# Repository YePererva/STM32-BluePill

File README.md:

# BluePill with USB type C

**NB! :** This a Work In Progress repository.

Here, I wanted to made a modification of the highly popular [STM32F103C8T6](https://www.st.com/resource/en/datasheet/stm32f103c8.pdf) development board, widely referred as [BluePill](https://stm32-base.org/boards/STM32F103C8T6-Blue-Pill.html).

The changes, I want(ed) to implement, are:
- replace the micro-USB slot with USB type C connector
- replace the 4-pin SWD programming connector with STDC-14 connector for compatibility with [ST-Link V3 mini](https://www.st.com/en/development-tools/stlink-v3mini.html) programmer
  - It should be compatible with 10-pin ARM cortex programming connector
  - I want to wire the SWO connectivity for more debug options
- Add [QWIIC](https://www.sparkfun.com/products/14417) connector for easier I2C sensor boards connection (like on [Sparkfun](https://www.sparkfun.com/qwiic#products) boards)
- replace the jumpers for boot options with tactile buttons (like on another variation of BluePill made by a seller from [TaoBao](https://ydsd1.oss-cn-shenzhen.aliyuncs.com/STM32F1/103C8V1.1.rar) )
- add power protection to USB against external power source (thinking between diode or MOSFET connectivity)
- add the RTC power isolation
- replace the 8Mhz crystal with SMD (maybe, like on [MapleMini](https://github.com/leaflabs/maplemini) )
- add a option to use microcontroller not only in LQFP48 package, but UFQFPN48 package (alike [STM32F103CBU6](https://www.st.com/resource/en/datasheet/cd00161566.pdf))
- Replace the Power regulator. \
  Various versions of BluePill utilize either [RT9193-33](https://web.archive.org/web/20190316155227/http://wiki.stm32duino.com/index.php?title=Blue_Pill) or [TX6211B](https://stm32-base.org/boards/STM32F103C8T6-Blue-Pill), which are documented as < 300 mA power supply, but can overheat if used >100 mA.

With all of that, I also want to keep pin-to-pin compatibility with original BluePill and the final size of the board.

## What is inside the repository
- `project files` : folder with BluePill projects, implemented in KiCAD
  - `classic` : the "traditional" BluePill board, with some schematic fixes (wrong resistor value for USB pull-up, extra capacitor, etc.) and some "cosmetic" changes on board.
  - `reforged` : the board with fixes and functionality I want to add
- `references` : some references of schematics / issues / layouts I found

## Why I want to do it
- I want to practice with KiCAD
- I want electronics to be my hobby
- It is fun for me

# Afterwords
1. If you are looking for higher performance, take a look at STM32F411CE or STM32F401CC boards in similar form-factor (however, with different pinout) in [this](https://github.com/WeActTC/MiniF4-STM32F4x1) repository by WeAct Team.

2. WeAct Team also released a similar project for STM32F103CxT6 microcontroller and called it a [BluePill Plus](https://github.com/WeActTC/BluePill-Plus) with some differences:
  - not pin-to-pin compatible (right top pin near USB port is `+5V`, not `GND`)
  - the user LED moved to `PB2` pin, while should be attached `PC13`
  - extra user button, attached to `PA0`
  - extra solder place for SPI-Flash IC

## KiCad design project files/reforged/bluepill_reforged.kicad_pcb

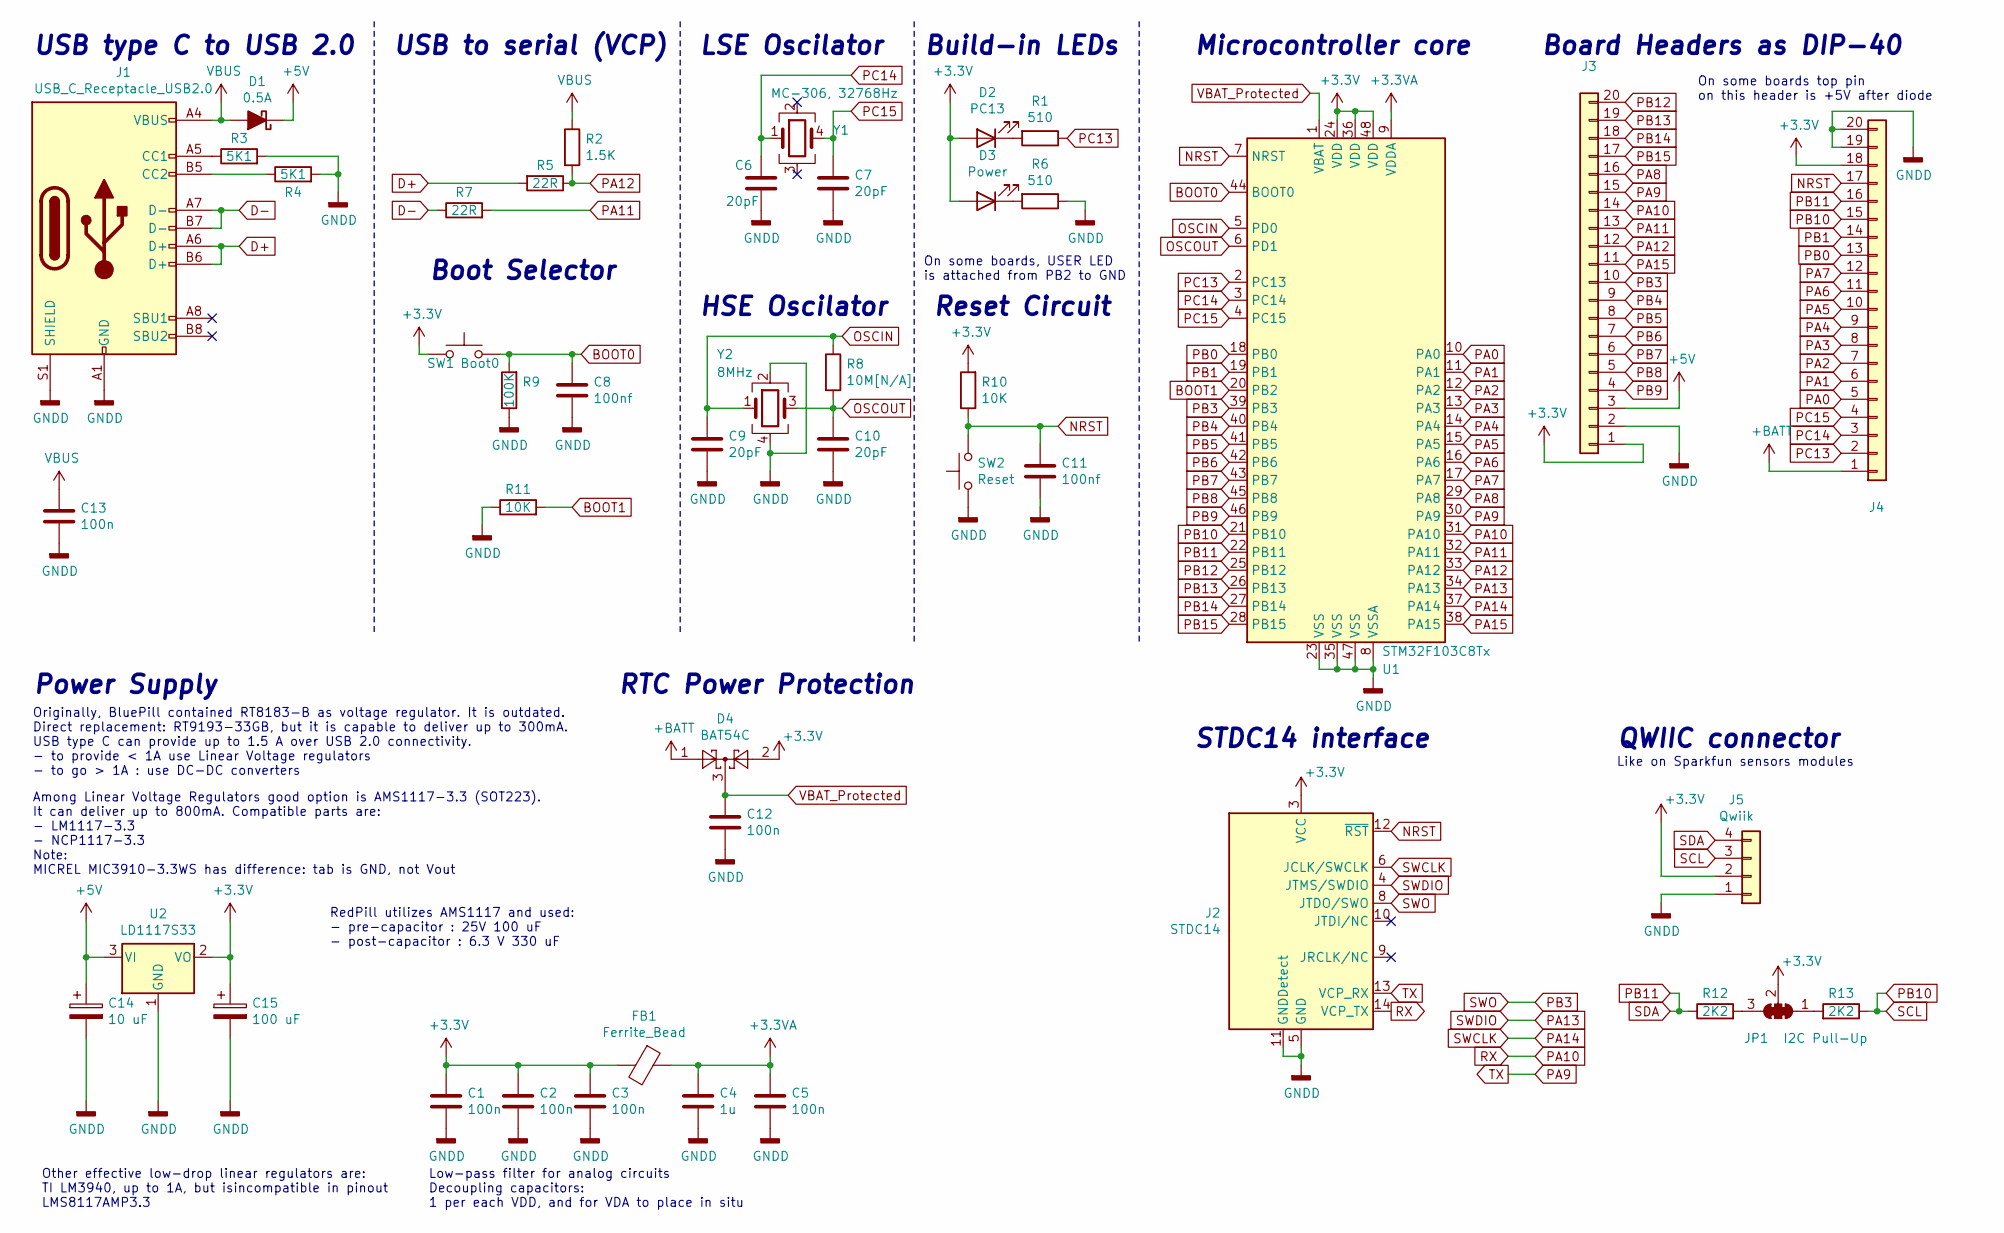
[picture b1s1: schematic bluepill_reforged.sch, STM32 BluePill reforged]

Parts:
C1, C2, C3, C5, C12, C13: 100n; C_0603_1608Metric
C4: 1u; C_0603_1608Metric
C6, C7, C9, C10: 20pF; C_0603_1608Metric
C8, C11: 100nf; C_0603_1608Metric
C14: 10 uF; CP_EIA-3528-12_Kemet-T
C15: 100 uF; CP_EIA-3528-12_Kemet-T
D1: 0.5A; D_SOD-128
D2: PC13; LED_0603_1608Metric_Castellated
D3: Power; LED_0603_1608Metric_Castellated
D4: BAT54C; SOT-23
FB1: Ferrite_Bead; L_0805_2012Metric
J1: USB_C_Receptacle_USB2.0; USB_C_Receptacle_Palconn_UTC16-G
J2: STDC14; PinHeader_2x07_P1.27mm_Vertical_SMD
J3: Left Castellation; PinHeader_1x20_P2.54mm_Vertical
J4: Right Castellation; PinHeader_1x20_P2.54mm_Vertical
J5: Qwiik; JST_SH_SM04B-SRSS-TB_1x04-1MP_P1.00mm_Horizontal
JP1: I2C Pull-Up; SolderJumper-3_P2.0mm_Open_TrianglePad1.0x1.5mm_NumberLabels
R1, R6: 510; R_0603_1608Metric
R2: 1.5K; R_0603_1608Metric
R3, R4: 5K1; R_0603_1608Metric
R5, R7: 22R; R_0603_1608Metric
R8: 10M[N/A]; R_0603_1608Metric
R9: 100K; R_0603_1608Metric
R10, R11: 10K; R_0603_1608Metric
R12, R13: 2K2; R_0603_1608Metric
SW1: Boot0; SW_SPST_B3U-1000P
SW2: Reset; SW_SPST_B3U-1000P
U1: STM32F103C8Tx; LQFP-48_7x7mm_P0.5mm
U2: LD1117S33; SOT-223-3_TabPin2
Y1: MC-306, 32768Hz; Crystal_SMD_SeikoEpson_MC306-4Pin_8.0x3.2mm
Y2: 8MHz; Crystal_SMD_TXC_7M-4Pin_3.2x2.5mm

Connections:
+3.3VA: C4.1, C5.1, FB1.1, U1.9 (VDDA)
+3V3: C1.1, C2.1, C3.1, C15.1, D2.2 (A), D3.2 (A), D4.2, FB1.2, J2.3 (VCC), J3.1, J4.18, J5.2, JP1.2 (C), R10.2, SW1.1, U1.24 (VDD), U1.36 (VDD), U1.48 (VDD), U2.2 (VO)
+5V: C14.1, D1.1 (K), J3.3, U2.3 (VI)
+BATT: D4.1, J4.1
BOOT0: C8.1, R9.2, SW1.2, U1.44 (BOOT0)
BOOT1: R11.2, U1.20 (PB2)
D+: J1.A6 (D+), J1.B6 (D+), R5.2
D-: J1.A7 (D-), J1.B7 (D-), R7.1
GNDD: C1.2, C2.2, C3.2, C4.2, C5.2, C6.2, C7.2, C8.2, C9.2, C10.2, C11.2, C12.2, C13.2, C14.2, C15.2, J1.A1 (GND), J1.A12 (GND), J1.B1 (GND), J1.B12 (GND), J1.S1 (SHIELD), J2.5 (GND), J2.7 (GND), J2.11 (GNDDetect), J3.2, J4.19, J4.20, J5.1, R3.2, R4.2, R6.1, R9.1, R11.1, SW2.1, U1.8 (VSSA), U1.23 (VSS), U1.35 (VSS), U1.47 (VSS), U2.1 (GND), Y2.2, Y2.4
NRST: C11.1, J2.12 (~RST), J4.17, R10.1, SW2.2, U1.7 (NRST)
unnamed: D2.1 (K), R1.2
unnamed: D3.1 (K), R6.2
unnamed: J1.A5 (CC1), R3.1
unnamed: J1.B5 (CC2), R4.1
unnamed: JP1.1 (A), R13.2
unnamed: JP1.3 (B), R12.2
OSCIN: C9.1, R8.1, U1.5 (PD0), Y2.1
OSCOUT: C10.1, R8.2, U1.6 (PD1), Y2.3
PA0: J4.5, U1.10 (PA0)
PA1: J4.6, U1.11 (PA1)
PA2: J4.7, U1.12 (PA2)
PA3: J4.8, U1.13 (PA3)
PA4: J4.9, U1.14 (PA4)
PA5: J4.10, U1.15 (PA5)
PA6: J4.11, U1.16 (PA6)
PA7: J4.12, U1.17 (PA7)
PA8: J3.16, U1.29 (PA8)
PA9: J2.13 (VCP_RX), J3.15, U1.30 (PA9)
PA10: J2.14 (VCP_TX), J3.14, U1.31 (PA10)
PA11: J3.13, R7.2, U1.32 (PA11)
PA12: J3.12, R2.2, R5.1, U1.33 (PA12)
PA13: J2.4 (JTMS/SWDIO), U1.34 (PA13)
PA14: J2.6 (JCLK/SWCLK), U1.37 (PA14)
PA15: J3.11, U1.38 (PA15)
PB0: J4.13, U1.18 (PB0)
PB1: J4.14, U1.19 (PB1)
PB3: J2.8 (JTDO/SWO), J3.10, U1.39 (PB3)
PB4: J3.9, U1.40 (PB4)
PB5: J3.8, U1.41 (PB5)
PB6: J3.7, U1.42 (PB6)
PB7: J3.6, U1.43 (PB7)
PB8: J3.5, U1.45 (PB8)
PB9: J3.4, U1.46 (PB9)
PB10: J4.15, J5.3, R13.1, U1.21 (PB10)
PB11: J4.16, J5.4, R12.1, U1.22 (PB11)
PB12: J3.20, U1.25 (PB12)
PB13: J3.19, U1.26 (PB13)
PB14: J3.18, U1.27 (PB14)
PB15: J3.17, U1.28 (PB15)
PC13: J4.2, R1.1, U1.2 (PC13)
PC14: C6.1, J4.3, U1.3 (PC14), Y1.1
PC15: C7.1, J4.4, U1.4 (PC15), Y1.4
VBAT_Protected: C12.1, D4.3, U1.1 (VBAT)
VBUS: C13.1, D1.2 (A), J1.A4 (VBUS), J1.A9 (VBUS), J1.B4 (VBUS), J1.B9 (VBUS), R2.1

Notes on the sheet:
Build-in LEDs
LSE Oscilator
HSE Oscilator
Among Linear Voltage Regulators good option is AMS1117-3.3 (SOT223). It can deliver up to 800mA. Compatible parts are: - LM1117-3.3 - NCP1117-3.3 Note: MICREL MIC3910-3.3WS has difference: tab is GND, not Vout
Other effective low-drop linear regulators are: TI LM3940, up to 1A, but isincompatible in pinout LMS8117AMP3.3
RedPill utilizes AMS1117 and used: - pre-capacitor : 25V 100 uF - post-capacitor : 6.3 V 330 uF
Board Headers as DIP-40
USB type C to USB 2.0
USB to serial (VCP)
Boot Selector
Microcontroller core
STDC14 interface
RTC Power Protection
Reset Circuit
Low-pass filter for analog circuits Decoupling capacitors: 1 per each VDD, and for VDA to place in situ
Power Supply
Originally, BluePill contained RT8183-B as voltage regulator. It is outdated. Direct replacement: RT9193-33GB, but it is capable to deliver up to 300mA. USB type C can provide up to 1.5 A over USB 2.0 connectivity. - to provide < 1A use Linear Voltage regulators - to go > 1A : use DC-DC converters
On some boards, USER LED is attached from PB2 to GND
On some boards top pin on this header is +5V after diode
QWIIC connector
Like on Sparkfun sensors modules

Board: 2 copper layers, 45 parts (28 on the bottom side), 54 nets, no tracks yet.

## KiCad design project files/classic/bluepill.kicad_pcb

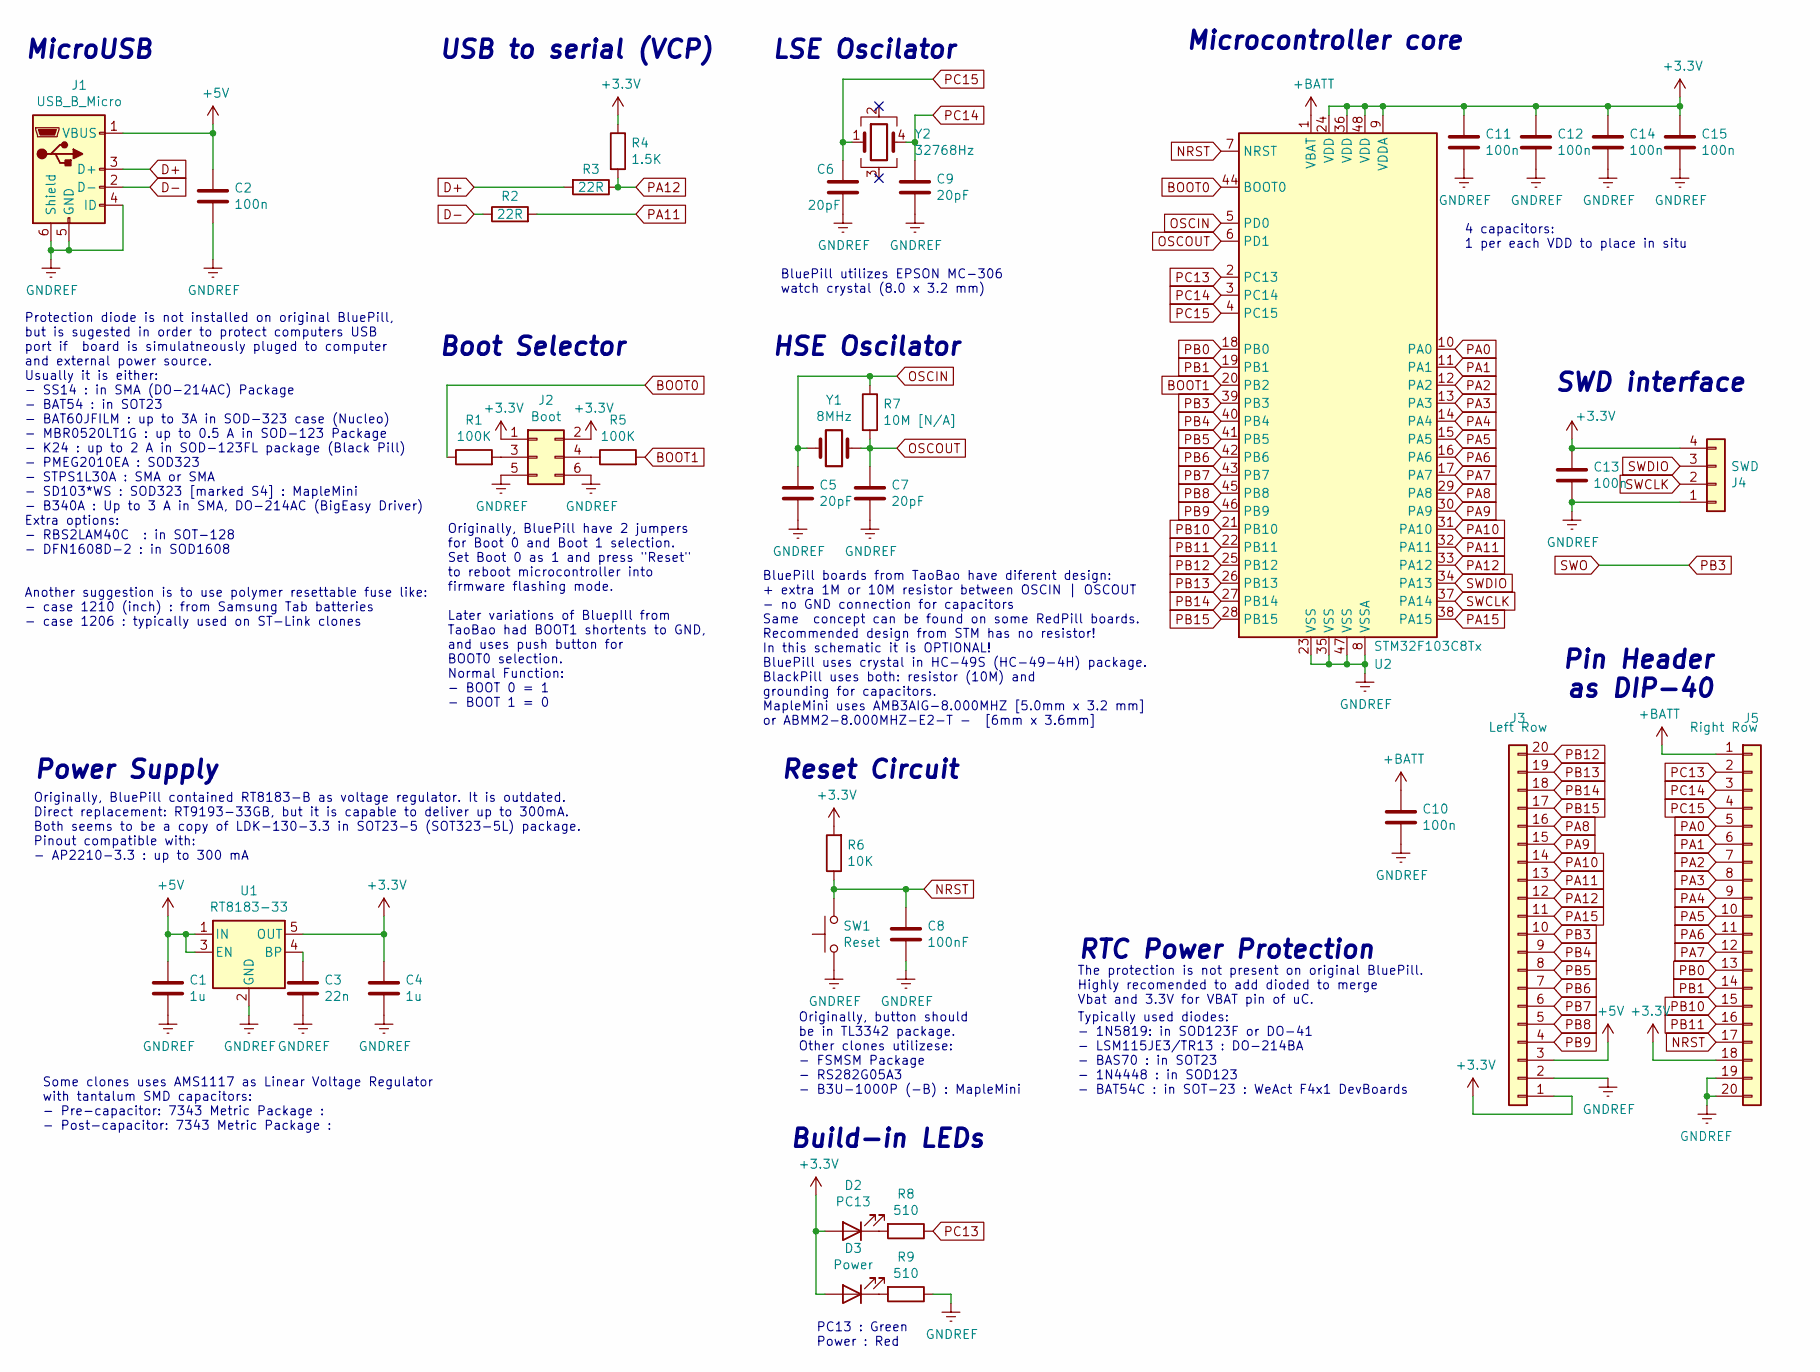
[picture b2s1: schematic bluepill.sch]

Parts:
C1: 1u; USB_Micro-B_Wuerth_629105150521
C2, C10, C11, C12, C13, C14, C15: 100n; C_0603_1608Metric
C3: 22n; C_0603_1608Metric
C4: 1u; C_0805_2012Metric
C5, C6, C7, C9: 20pF; C_0603_1608Metric
C8: 100nF; C_0603_1608Metric
D2: PC13; LED_0603_1608Metric_Castellated
D3: Power; LED_0603_1608Metric_Castellated
J1: USB_B_Micro
J2: Boot; PinHeader_2x03_P2.54mm_Vertical
J3: Left Row; PinHeader_1x20_P2.54mm_Vertical
J4: SWD; PinHeader_1x04_P2.54mm_Vertical
J5: Right Row; PinHeader_1x20_P2.54mm_Vertical
R1, R5: 100K; R_0603_1608Metric
R2, R3: 22R; R_0603_1608Metric
R4: 1.5K; R_0603_1608Metric
R6: 10K; R_0603_1608Metric
R7: 10M [N/A]; R_0603_1608Metric
R8, R9: 510; R_0603_1608Metric
SW1: Reset; SW_SPST_TL3342
U1: RT8183-33; SOT-353_SC-70-5
U2: STM32F103C8Tx; LQFP-48_7x7mm_P0.5mm
Y1: 8MHz; Crystal_HC49-4H_Vertical
Y2: 32768Hz; Crystal_SMD_SeikoEpson_MC306-4Pin_8.0x3.2mm

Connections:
+3V3: C4.2, C11.1, C12.1, C13.2, C14.1, C15.1, D2.2 (A), D3.2 (A), J2.1, J2.2, J3.1, J4.4, J5.18, R4.1, R6.2, U1.5 (OUT), U2.9 (VDDA), U2.24 (VDD), U2.36 (VDD), U2.48 (VDD)
+5V: C1.2, C2.1, J1.1 (VBUS), J3.3, U1.1 (IN), U1.3 (EN)
+BATT: C10.1, J5.1, U2.1 (VBAT)
BOOT0: R1.1, U2.44 (BOOT0)
BOOT1: R5.2, U2.20 (PB2)
D+: J1.3 (D+), R3.2
D-: J1.2 (D-), R2.1
GNDREF: C1.1, C2.2, C3.1, C4.1, C5.2, C6.2, C7.2, C8.2, C9.2, C10.2, C11.2, C12.2, C13.1, C14.2, C15.2, J1.4 (ID), J1.5 (GND), J1.6 (Shield), J2.5, J2.6, J3.2, J4.1, J5.19, J5.20, R9.1, SW1.1, U1.2 (GND), U2.8 (VSSA), U2.23 (VSS), U2.35 (VSS), U2.47 (VSS)
NRST: C8.1, J5.17, R6.1, SW1.2, U2.7 (NRST)
unnamed: C3.2, U1.4 (BP)
unnamed: D2.1 (K), R8.2
unnamed: D3.1 (K), R9.2
unnamed: J2.3, R1.2
unnamed: J2.4, R5.1
OSCIN: C5.1, R7.1, U2.5 (PD0), Y1.2
OSCOUT: C7.1, R7.2, U2.6 (PD1), Y1.1
PA0: J5.5, U2.10 (PA0)
PA1: J5.6, U2.11 (PA1)
PA2: J5.7, U2.12 (PA2)
PA3: J5.8, U2.13 (PA3)
PA4: J5.9, U2.14 (PA4)
PA5: J5.10, U2.15 (PA5)
PA6: J5.11, U2.16 (PA6)
PA7: J5.12, U2.17 (PA7)
PA8: J3.16, U2.29 (PA8)
PA9: J3.15, U2.30 (PA9)
PA10: J3.14, U2.31 (PA10)
PA11: J3.13, R2.2, U2.32 (PA11)
PA12: J3.12, R3.1, R4.2, U2.33 (PA12)
PA15: J3.11, U2.38 (PA15)
PB0: J5.13, U2.18 (PB0)
PB1: J5.14, U2.19 (PB1)
PB3: J3.10, U2.39 (PB3)
PB4: J3.9, U2.40 (PB4)
PB5: J3.8, U2.41 (PB5)
PB6: J3.7, U2.42 (PB6)
PB7: J3.6, U2.43 (PB7)
PB8: J3.5, U2.45 (PB8)
PB9: J3.4, U2.46 (PB9)
PB10: J5.15, U2.21 (PB10)
PB11: J5.16, U2.22 (PB11)
PB12: J3.20, U2.25 (PB12)
PB13: J3.19, U2.26 (PB13)
PB14: J3.18, U2.27 (PB14)
PB15: J3.17, U2.28 (PB15)
PC13: J5.2, R8.1, U2.2 (PC13)
PC14: C9.1, J5.3, U2.3 (PC14), Y2.4
PC15: C6.1, J5.4, U2.4 (PC15), Y2.1
SWCLK: J4.2, U2.37 (PA14)
SWDIO: J4.3, U2.34 (PA13)

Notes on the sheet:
LSE Oscilator
HSE Oscilator
Originally, BluePill have 2 jumpers for Boot 0 and Boot 1 selection. Set Boot 0 as 1 and press "Reset" to reboot microcontroller into firmware flashing mode. Later variations of BluepIll from TaoBao had BOOT1 shortents to GND, and uses push button for BOOT0 selection. Normal Function: - BOOT 0 = 1 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
Protection diode is not installed on original BluePill, but is sugested in order to protect computers USB port if board is simulatneously pluged to computer and external power source. Usually it is either: - SS14 : in SMA (DO-214AC) Package - BAT54 : in SOT23 - BAT60JFILM : up to 3A in SOD-323 case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
Pin Header as DIP-40
BluePill utilizes EPSON MC-306 watch crystal (8.0 x 3.2 mm)
MicroUSB
USB to serial (VCP)
Boot Selector
Microcontroller core
SWD interface
BluePill boards from TaoBao have diferent design: + extra 1M or 10M resistor between OSCIN | OSCOUT - no GND connection for capacitors Same concept can be found on some RedPill boards. Recommended design from STM has no resistor! In this schematic it is OPTIONAL! BluePill uses crystal in HC-49S (HC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
Reset Circuit
4 capacitors: 1 per each VDD to place in situ
Power Supply
Originally, BluePill contained RT8183-B as voltage regulator. It is outdated. Direct replacement: RT9193-33GB, but it is capable to deliver up to 300mA. Both seems to be a copy of LDK-130-3.3 in SOT23-5 (SOT323-5L) package. Pinout compatible with: - AP2210-3.3 : up to 300 mA
Originally, button should be in TL3342 package. Other clones utilizese: - FSMSM Package - RS282G05A3 - B3U-1000P (-B) : MapleMini
Some clones uses AMS1117 as Linear Voltage Regulator with tantalum SMD capacitors: - Pre-capacitor: 7343 Metric Package : - Post-capacitor: 7343 Metric Package :
Another suggestion is to use polymer resettable fuse like: - case 1210 (inch) : from Samsung Tab batteries - case 1206 : typically used on ST-Link clones
PC13 : Green Power : Red
Build-in LEDs
The protection is not present on original BluePill. Highly recomended to add dioded to merge Vbat and 3.3V for VBAT pin of uC.
Typically used diodes: - 1N5819: in SOD123F or DO-41 - LSM115JE3/TR13 : DO-214BA - BAS70 : in SOT23 - 1N4448 : in SOD123 - BAT54C : in SOT-23 : WeAct F4x1 DevBoards
RTC Power Protection

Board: 2 copper layers, 35 parts (26 on the bottom side), 48 nets, no tracks yet.

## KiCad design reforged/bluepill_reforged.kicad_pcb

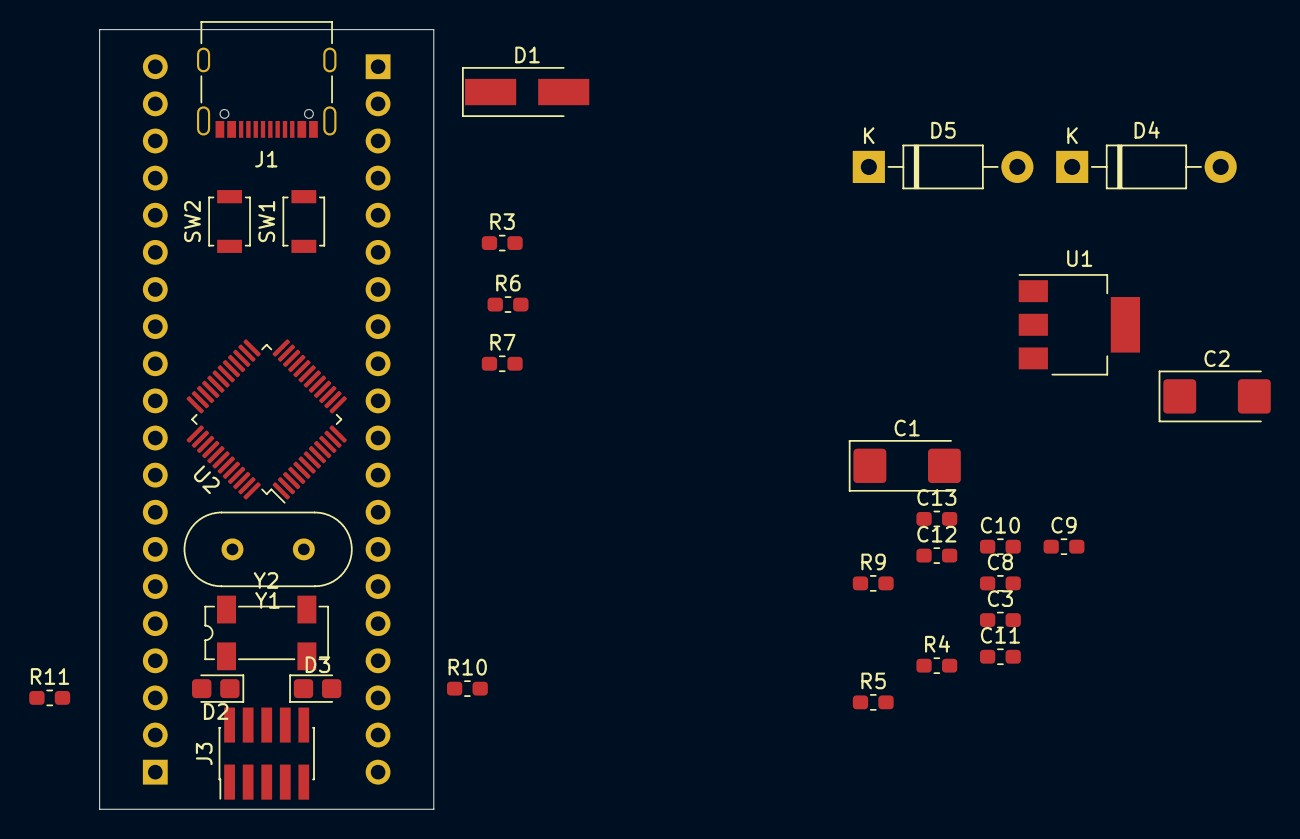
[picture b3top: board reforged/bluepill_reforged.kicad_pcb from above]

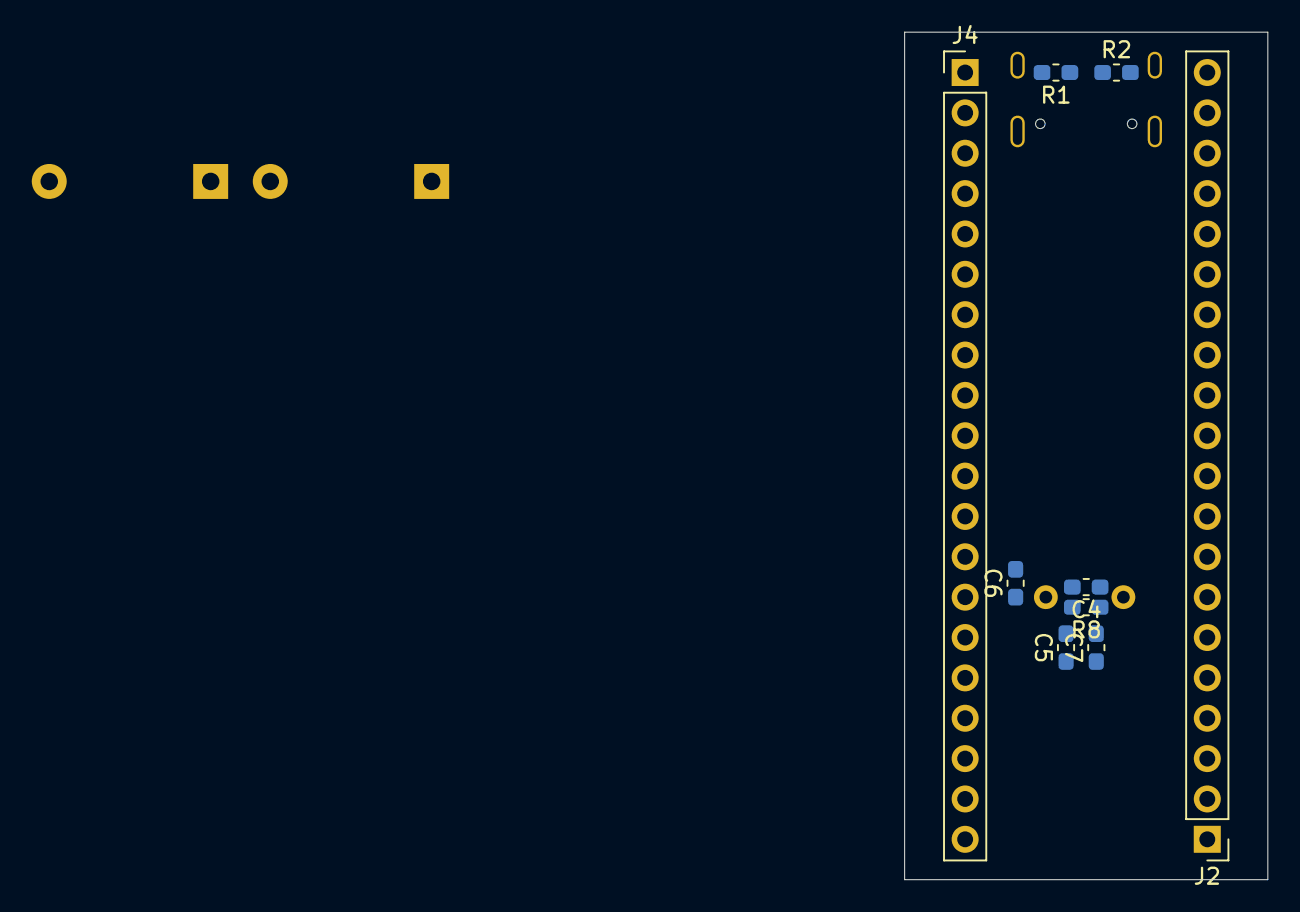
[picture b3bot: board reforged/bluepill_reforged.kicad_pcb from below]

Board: 2 copper layers, 22.9 x 53.3 mm, 39 parts (9 on the bottom side), 51 nets, no tracks yet.

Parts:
C1: 0.1-10 uF; CP_EIA-6032-20_AVX-F_Pad2.25x2.35mm_HandSolder
C2: 47-1000 uF; CP_EIA-6032-20_AVX-F_Pad2.25x2.35mm_HandSolder
C3, C8: 1uF; C_0603_1608Metric_Pad1.05x0.95mm_HandSolder
C4, C5, C6, C7: 20pF; C_0603_1608Metric_Pad1.05x0.95mm_HandSolder
C9, C10, C11, C12, C13: 100n; C_0603_1608Metric_Pad1.05x0.95mm_HandSolder
D1: Protection; D_SMA_Handsoldering
D2: Green; LED_0805_2012Metric_Castellated
D3: Power; LED_0805_2012Metric_Castellated
D4, D5: 1N5819; D_DO-41_SOD81_P10.16mm_Horizontal
J1: USB_C_Receptacle_USB2.0; USB_C_Receptacle_Palconn_UTC16-G
J2: Left Castellation; PinHeader_1x20_P2.54mm_Vertical
J3: Cortex debug; PinHeader_2x05_P1.27mm_Vertical_SMD
J4: Right Castellation; PinHeader_1x20_P2.54mm_Vertical
R1, R2: 5K1; R_0603_1608Metric_Pad1.05x0.95mm_HandSolder
R3, R6: 22R; R_0603_1608Metric_Pad1.05x0.95mm_HandSolder
R4: 100K; R_0603_1608Metric_Pad1.05x0.95mm_HandSolder
R5, R9: 10K; R_0603_1608Metric_Pad1.05x0.95mm_HandSolder
R7: 1.5K; R_0603_1608Metric_Pad1.05x0.95mm_HandSolder
R8: 10M [N/A]; R_0603_1608Metric_Pad1.05x0.95mm_HandSolder
R10, R11: 510; R_0603_1608Metric_Pad1.05x0.95mm_HandSolder
SW1: Boot0; SW_SPST_B3U-1000P
SW2: Reset; SW_SPST_B3U-1000P
U1: AMS1117-3.3; SOT-223-3_TabPin2
U2: STM32F103C8Tx; LQFP-48_7x7mm_P0.5mm
Y1: 8MHz; Crystal_HC49-4H_Vertical
Y2: 32768Hz; Crystal_SMD_SeikoEpson_MC306-4Pin_8.0x3.2mm

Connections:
+3V3: C2.1, C10.1, C11.1, C12.1, C13.1, D2.2, D3.2, D5.2, J2.1, J3.1, J4.3, R7.1, R9.2, SW1.1, U1.2, U2.9, U2.24, U2.36, U2.48
+5V: C1.1, D1.1, J2.3, U1.3
+BATT: D4.2, J4.20
BOOT0: C3.1, R4.2, SW1.2, U2.44
BOOT1: R5.2, U2.20
D+: J1.A6, J1.B6, R6.2
D-: J1.A7, J1.B7, R3.1
GNDREF: C1.2, C2.2, C3.2, C4.2, C5.2, C6.2, C7.2, C8.2, C9.2, C10.2, C11.2, C12.2, C13.2, J1.A1, J1.A12, J1.B1, J1.B12, J1.S1, J2.2, J3.3, J3.5, J3.9, J4.1, J4.2, R1.2, R2.2, R4.1, R5.1, R11.1, SW2.1, U1.1, U2.8, U2.23, U2.35, U2.47
NRST: C8.1, J3.10, J4.4, R9.1, SW2.2, U2.7
unnamed: D2.1, R10.2
unnamed: D3.1, R11.2
unnamed: J1.A5, R1.1
unnamed: J1.B5, R2.1
OSCIN: C4.1, R8.1, U2.5, Y1.2
OSCOUT: C6.1, R8.2, U2.6, Y1.1
PA0: J4.16, U2.10
PA1: J4.15, U2.11
PA2: J4.14, U2.12
PA3: J4.13, U2.13
PA4: J4.12, U2.14
PA5: J4.11, U2.15
PA6: J4.10, U2.16
PA7: J4.9, U2.17
PA8: J2.16, U2.29
PA9: J2.15, U2.30
PA10: J2.14, U2.31
PA11: J2.13, R3.2, U2.32
PA12: J2.12, R6.1, R7.2, U2.33
PA13: J3.2, U2.34
PA14: J3.4, U2.37
PA15: J2.11, U2.38
PB0: J4.8, U2.18
PB1: J4.7, U2.19
PB3: J2.10, J3.6, U2.39
PB4: J2.9, U2.40
PB5: J2.8, U2.41
PB6: J2.7, U2.42
PB7: J2.6, U2.43
PB8: J2.5, U2.45
PB9: J2.4, U2.46
PB10: J4.6, U2.21
PB11: J4.5, U2.22
PB12: J2.20, U2.25
PB13: J2.19, U2.26
PB14: J2.18, U2.27
PB15: J2.17, U2.28
PC13: J4.19, R10.1, U2.2
PC14: C5.1, J4.18, U2.3, Y2.1
PC15: C7.1, J4.17, U2.4, Y2.4
VBAT_Protected: C9.1, D4.1, D5.1, U2.1
VBUS: D1.2, J1.A4, J1.A9, J1.B4, J1.B9

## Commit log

2020-01-07 basic schematic
2020-01-07 references
2020-01-07 re-arrangements
2020-01-07 re-arrangement + updated description
2020-01-08 replaced SWD 10 with 14
2020-01-09 re-routing
2020-01-21 minor
2020-01-26 minor updates
2020-03-10 V1.1 rearrangements
2020-03-10 manufacturer updates
2020-03-10 replaced crystal with smd
2020-08-05 rearranged
2020-08-05 edits
2020-10-22 Added Readme.md and minor changes to classic layout
2020-10-23 Updates after re-opening in KiCAD 5.1.7
2020-10-25 Replaced the symbol of STDC14
2020-11-11 couple comments
2020-11-16 Added another modification
2020-12-06 Added lo-pass filter for VCCA
2020-12-09 Added QWIIC connector
2021-02-03 push when github lagged
